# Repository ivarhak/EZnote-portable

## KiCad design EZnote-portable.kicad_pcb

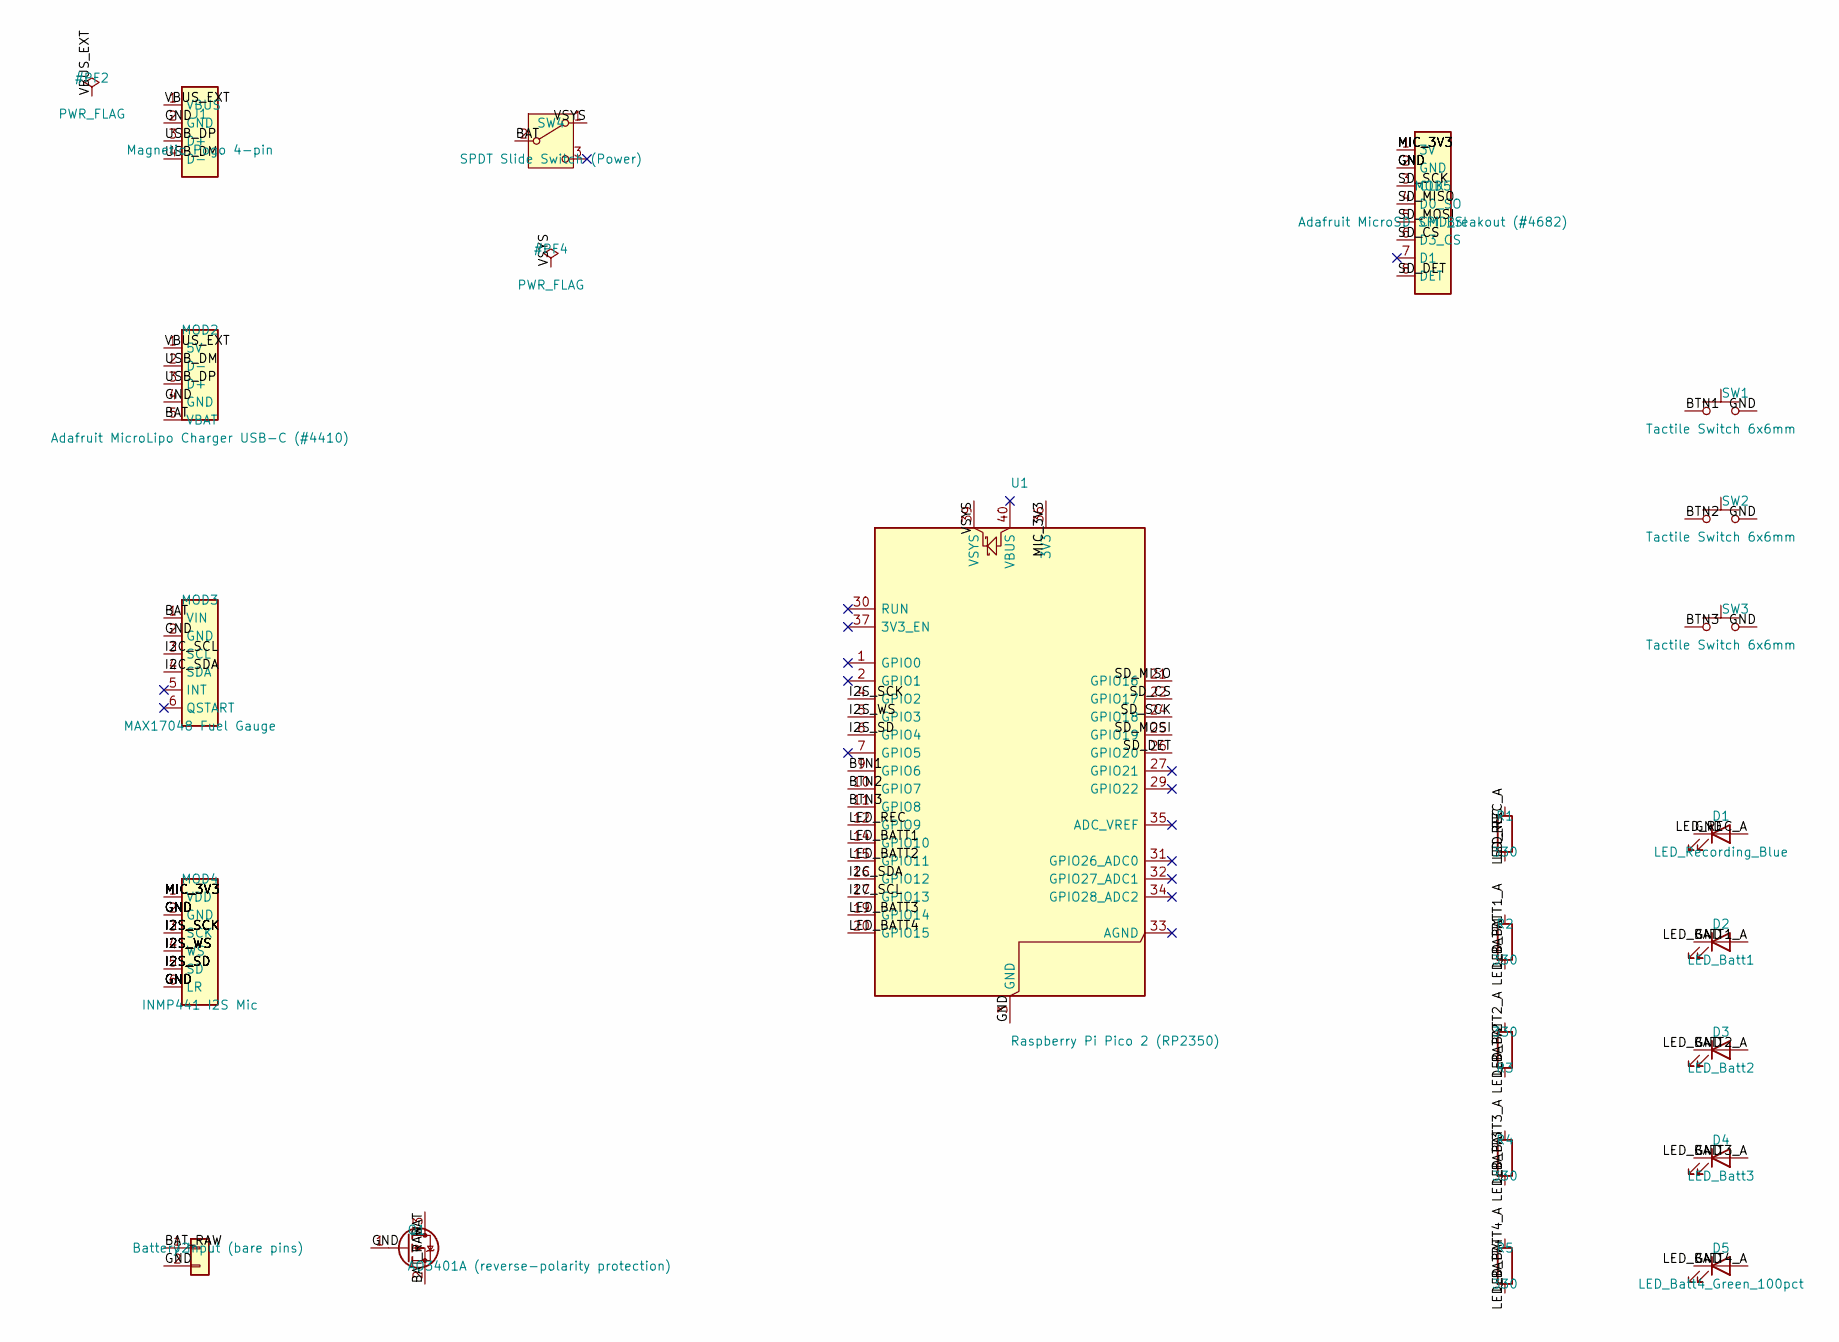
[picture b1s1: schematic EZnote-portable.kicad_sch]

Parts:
D1: LED_Recording_Blue; LED_0805_2012Metric
D2: LED_Batt1; LED_0805_2012Metric
D3: LED_Batt2; LED_0805_2012Metric
D4: LED_Batt3; LED_0805_2012Metric
D5: LED_Batt4_Green_100pct; LED_0805_2012Metric
J1: Magnetic Pogo 4-pin; Pogo_4Pin_2.54mm
J2: Battery Input (bare pins); PinHeader_1x02_P2.54mm_Vertical
MOD2: Adafruit MicroLipo Charger USB-C (#4410); Adafruit_MicroLipo_Outline
MOD3: MAX17048 Fuel Gauge; MAX17048_Breakout_Outline
MOD4: INMP441 I2S Mic; INMP441_Breakout_Outline
MOD5: Adafruit MicroSD SPI Breakout (#4682); Adafruit_MicroSD_Outline
Q1: AO3401A (reverse-polarity protection); SOT-23
R1, R2, R3, R4, R5: 330; R_0805_2012Metric
SW1, SW2, SW3: Tactile Switch 6x6mm; SW_Tactile_SPST_Angled_PTS645Vx31-2LFS
SW4: SPDT Slide Switch (Power); SW_E-Switch_EG1224_SPDT_Angled
U1: Raspberry Pi Pico 2 (RP2350); RaspberryPi_Pico_Common_THT

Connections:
/BAT: MOD2.5 (VBAT), MOD3.1 (VIN), Q1.3 (D), SW4.2 (B)
/BAT_RAW: J2.1, Q1.2 (S)
/BTN1: SW1.1, U1.9 (GPIO6)
/BTN2: SW2.1, U1.10 (GPIO7)
/BTN3: SW3.1, U1.11 (GPIO8)
/GND: D1.1 (K), D2.1 (K), D3.1 (K), D4.1 (K), D5.1 (K), J1.2 (GND), J2.2, MOD2.4 (GND), MOD3.2 (GND), MOD4.2 (GND), MOD4.6 (LR), MOD5.2 (GND), Q1.1 (G), SW1.2, SW2.2, SW3.2, U1.3 (GND), U1.8 (GND), U1.13 (GND), U1.18 (GND), U1.23 (GND), U1.28 (GND), U1.38 (GND)
/I2C_SCL: MOD3.3 (SCL), U1.17 (GPIO13)
/I2C_SDA: MOD3.4 (SDA), U1.16 (GPIO12)
/I2S_SCK: MOD4.3 (SCK), U1.4 (GPIO2)
/I2S_SD: MOD4.5 (SD), U1.6 (GPIO4)
/I2S_WS: MOD4.4 (WS), U1.5 (GPIO3)
/LED_BATT1: R2.1, U1.14 (GPIO10)
/LED_BATT1_A: D2.2 (A), R2.2
/LED_BATT2: R3.2, U1.15 (GPIO11)
/LED_BATT2_A: D3.2 (A), R3.1
/LED_BATT3: R4.1, U1.19 (GPIO14)
/LED_BATT3_A: D4.2 (A), R4.2
/LED_BATT4: R5.1, U1.20 (GPIO15)
/LED_BATT4_A: D5.2 (A), R5.2
/LED_REC: R1.1, U1.12 (GPIO9)
/LED_REC_A: D1.2 (A), R1.2
/MIC_3V3: MOD4.1 (VDD), MOD5.1 (3V), U1.36 (3V3)
/SD_CS: MOD5.6 (D3_CS), U1.22 (GPIO17)
/SD_DET: MOD5.8 (DET), U1.26 (GPIO20)
/SD_MISO: MOD5.4 (D0_SO), U1.21 (GPIO16)
/SD_MOSI: MOD5.5 (CMD_SI), U1.25 (GPIO19)
/SD_SCK: MOD5.3 (CLK), U1.24 (GPIO18)
/USB_DM: J1.4 (D-), MOD2.2 (D-)
/USB_DP: J1.3 (D+), MOD2.3 (D+)

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
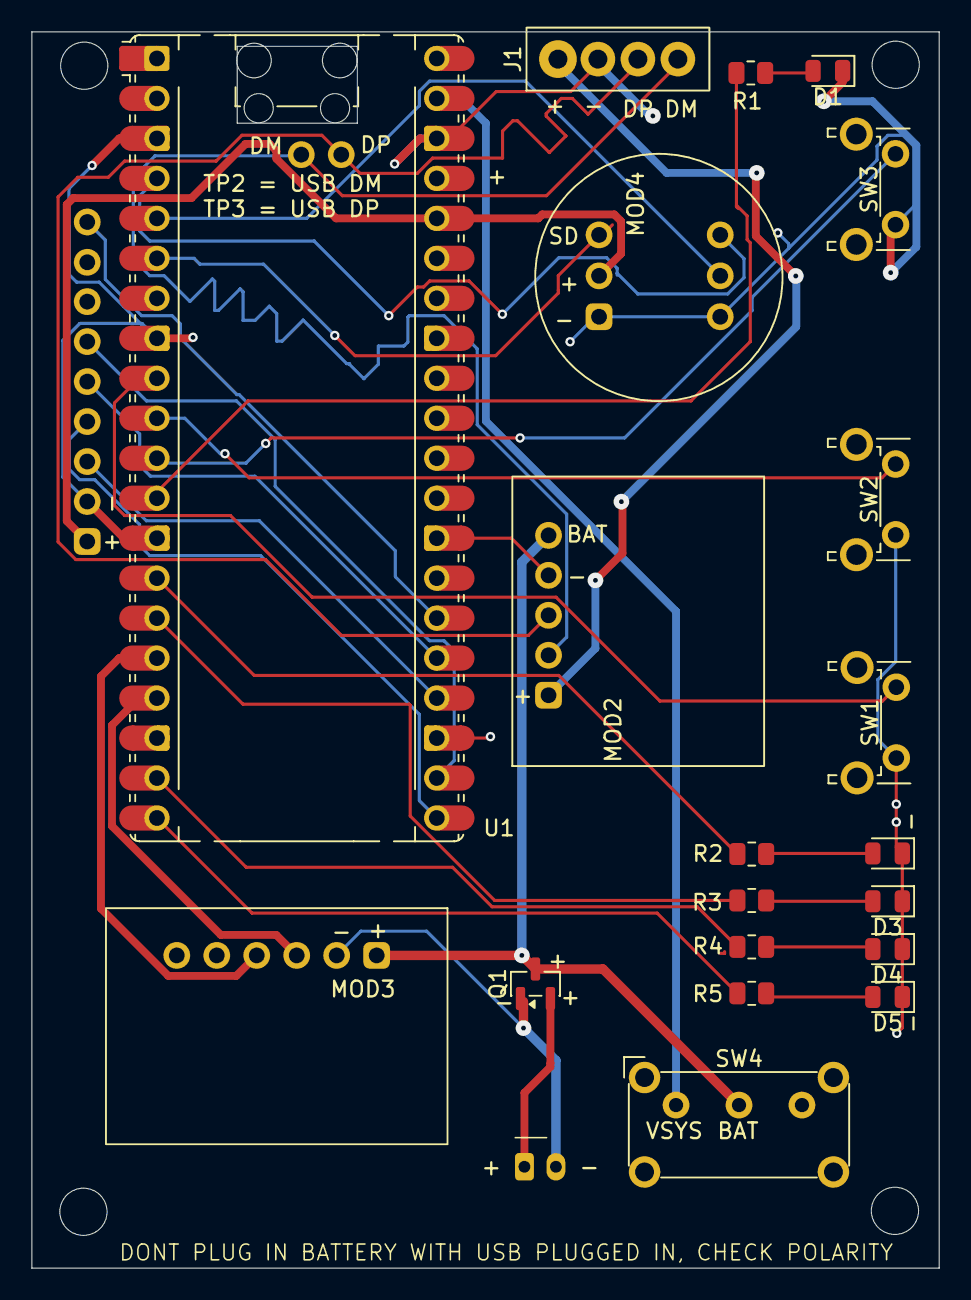
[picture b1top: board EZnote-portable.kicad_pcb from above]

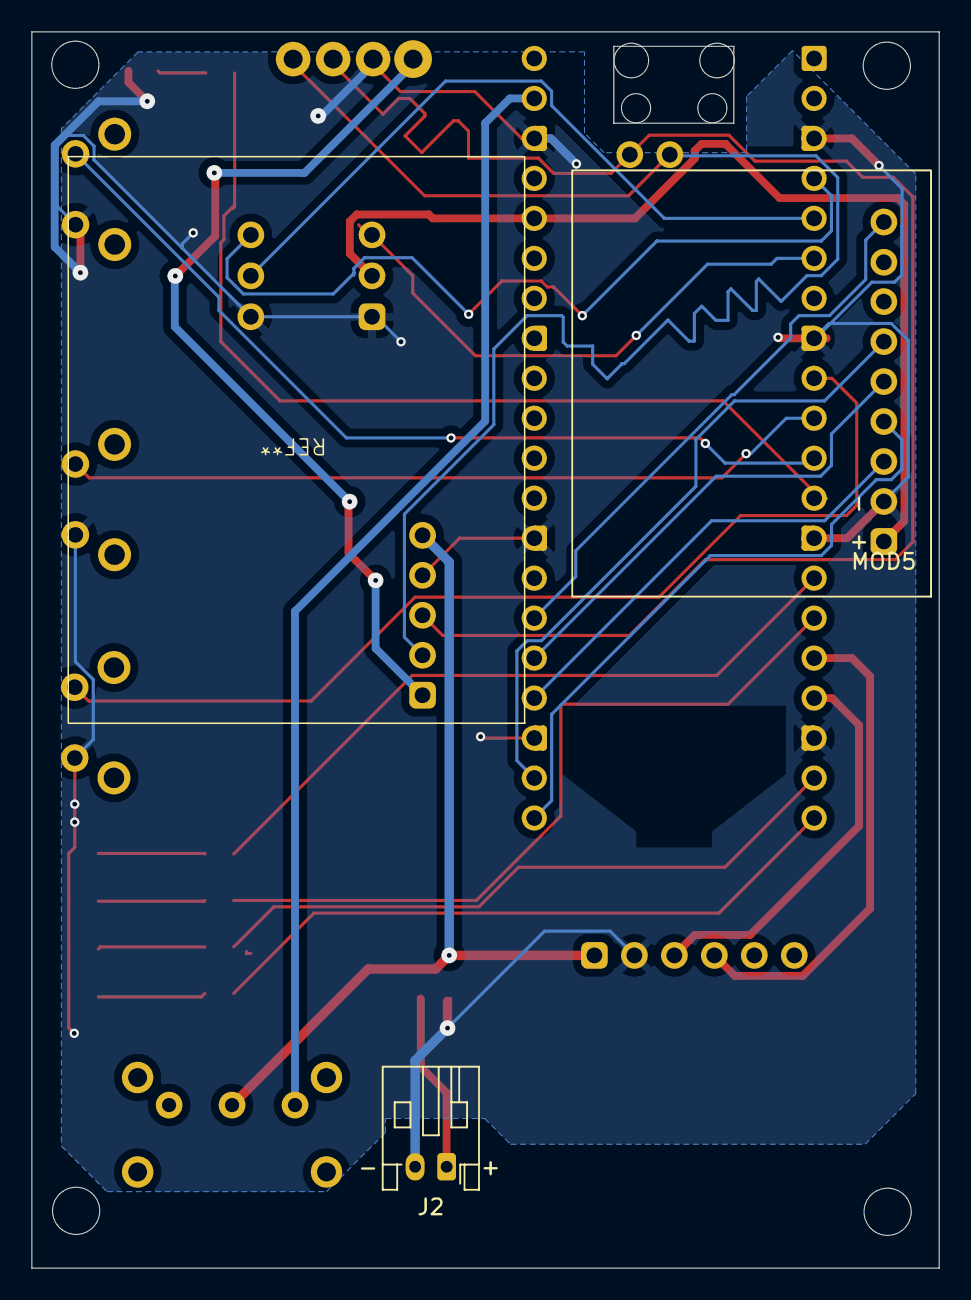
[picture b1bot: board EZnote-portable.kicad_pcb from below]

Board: 2 copper layers, 57.6 x 78.6 mm, 22 parts (2 on the bottom side), 31 nets.
